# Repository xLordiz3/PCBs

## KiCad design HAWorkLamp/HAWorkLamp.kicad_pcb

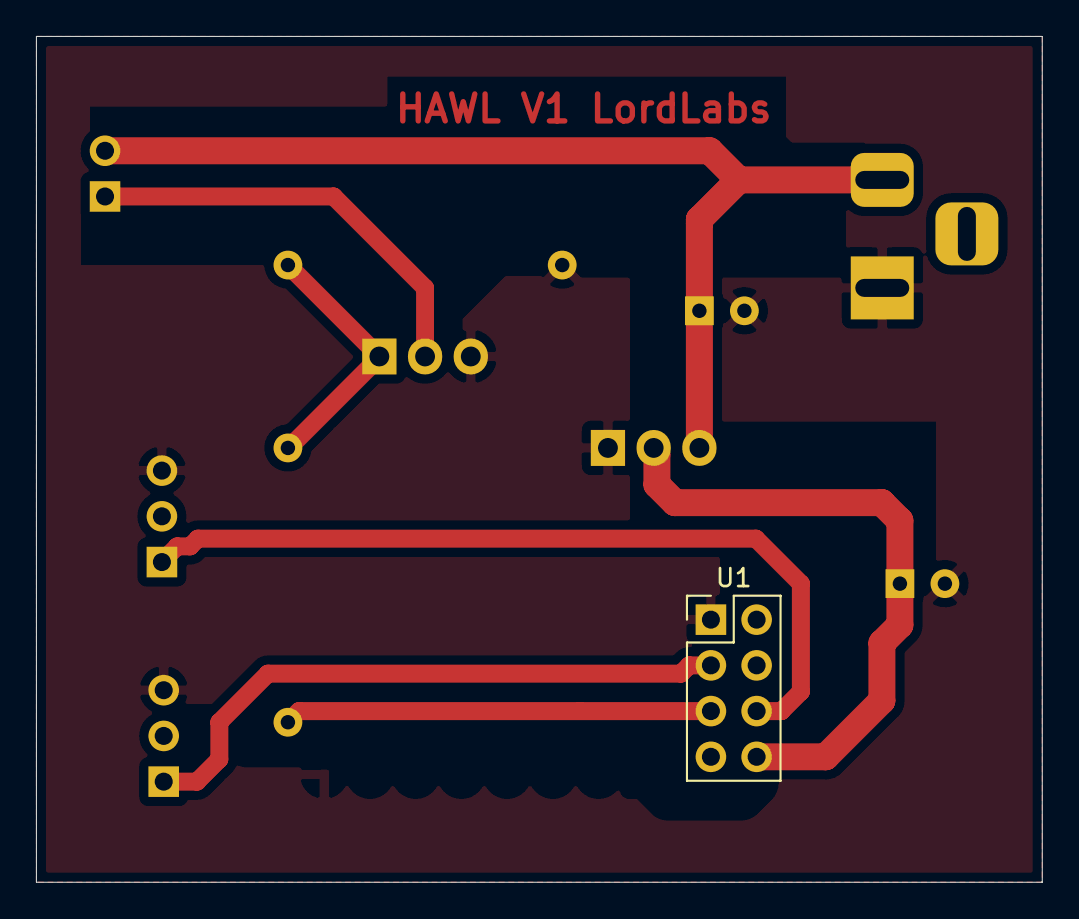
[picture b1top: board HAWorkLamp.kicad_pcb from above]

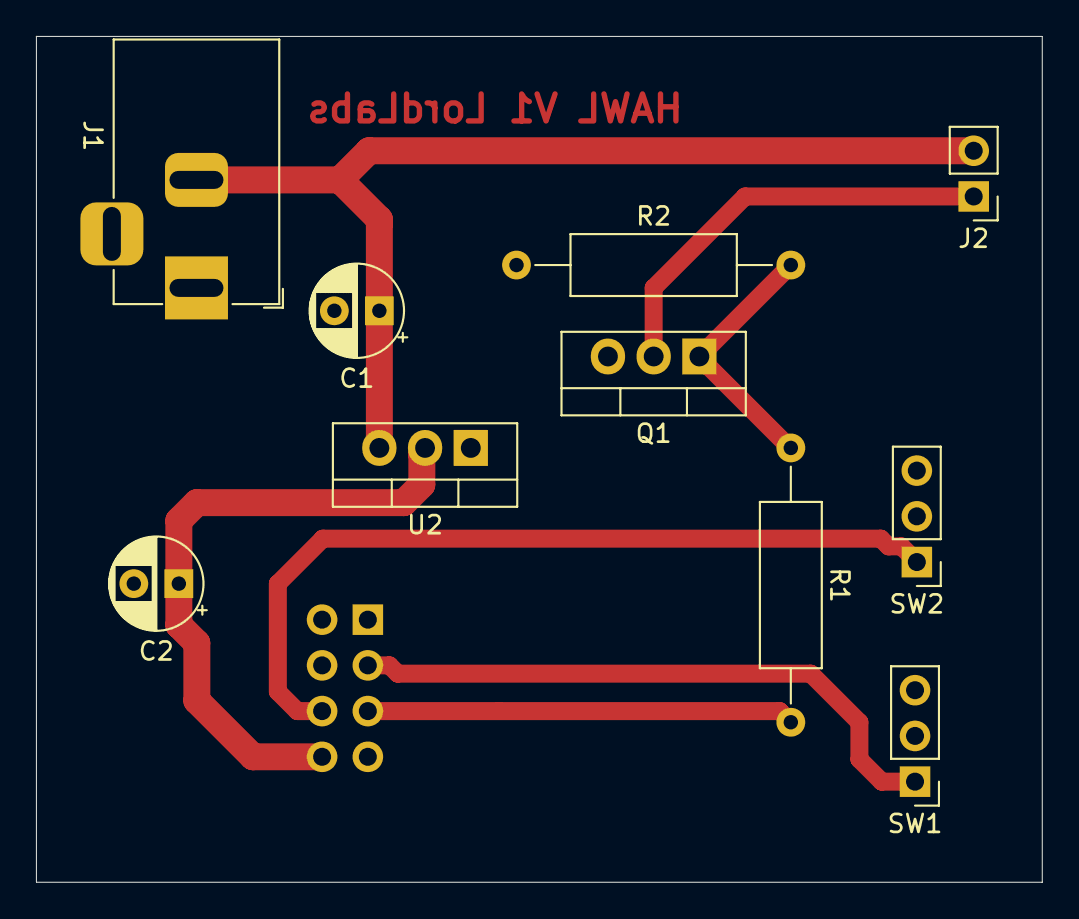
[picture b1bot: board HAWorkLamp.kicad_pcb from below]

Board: 2 copper layers, 55.9 x 47.0 mm, 11 parts (10 on the bottom side), 8 nets.

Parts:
C1, C2: CP; CP_Radial_D5.0mm_P2.50mm
J1: Jack-DC; BarrelJack_Horizontal
J2: LED Connection; PinHeader_1x02_P2.54mm_Vertical
Q1: FQP30N06L; TO-220-3_Vertical
R1: 220R; R_Axial_DIN0309_L9.0mm_D3.2mm_P15.24mm_Horizontal
R2: 100K; R_Axial_DIN0309_L9.0mm_D3.2mm_P15.24mm_Horizontal
SW1: Power switch; PinHeader_1x03_P2.54mm_Vertical
SW2: Reset Switch; PinHeader_1x03_P2.54mm_Vertical
U1: ESP8266; PinHeader_2x04_P2.54mm_Vertical
U2: LM1117-3.3; TO-220-3_Vertical

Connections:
+3V3: C2.1, U1.8, U2.2
+12V: C1.1, J1.2, J2.2, U2.3
/GPIO0: R1.2, U1.5
/GPIO2: SW1.1, U1.3
/RST: SW2.1, U1.6
GND: C1.2, C2.2, J1.1, Q1.3, R2.1, SW1.2, SW2.2, U1.1, U2.1
unnamed: J2.1, Q1.2
unnamed: Q1.1, R1.1, R2.2

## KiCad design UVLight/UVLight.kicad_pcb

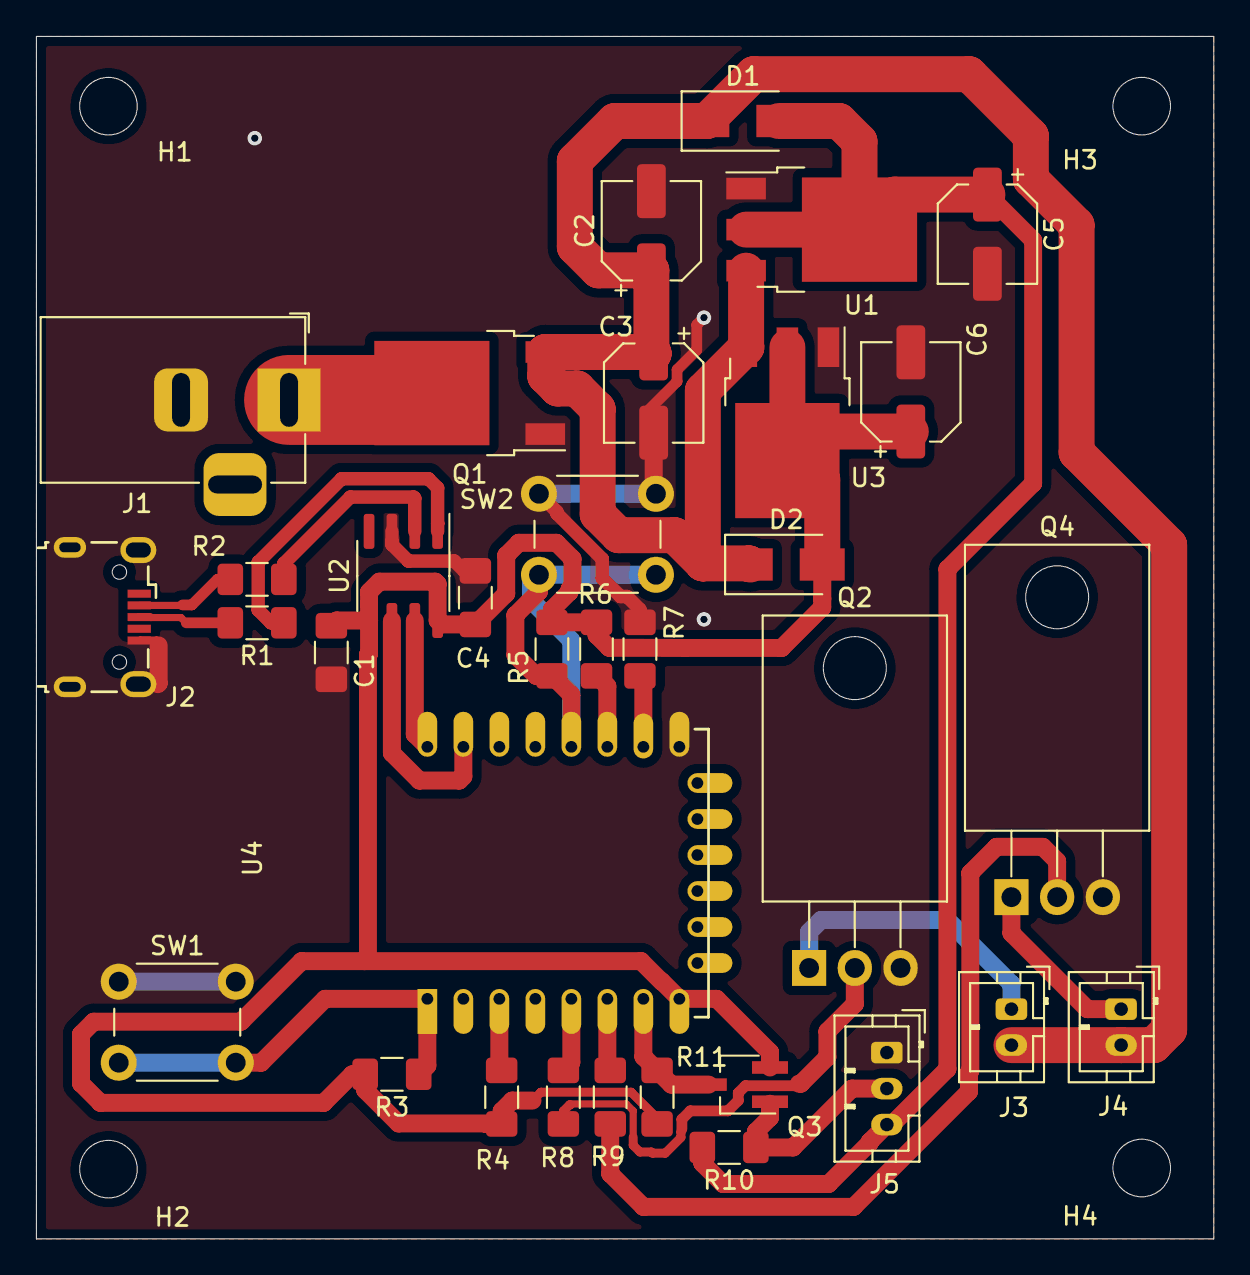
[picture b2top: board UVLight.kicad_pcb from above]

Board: 2 copper layers, 65.4 x 66.8 mm, 38 parts (0 on the bottom side), 24 nets.

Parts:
C1, C4: C 100nF; C_1206_3216Metric_Pad1.42x1.75mm_HandSolder
C2, C3, C5, C6: C 10uF; CP_Elec_5x5.4
D1, D2: 1N4002; D_SMA
H1, H2, H3, H4: MountingHole; MountingHole_3.2mm_M3
J1: Barrel_Jack_MountingPin; BarrelJack_Horizontal
J2: USB_B_Micro; USB_Micro-B_Wuerth_629105150521
J3, J4: Conn_01x02_Male; JST_PH_B2B-PH-K_1x02_P2.00mm_Vertical
J5: Conn_01x03_Male; JST_PH_B3B-PH-K_1x03_P2.00mm_Vertical
Q1: FQP47P06; TO-252-2
Q2, Q4: FQP30N06L; TO-220-3_Horizontal_TabDown
Q3: BS170; SOT-23W_Handsoldering
R1, R2: R 22; R_1206_3216Metric_Pad1.42x1.75mm_HandSolder
R3, R4, R5, R6, R7: R 10K; R_1206_3216Metric_Pad1.42x1.75mm_HandSolder
R8, R9: R; R_1206_3216Metric_Pad1.42x1.75mm_HandSolder
R10, R11: R 4.7K; R_1206_3216Metric_Pad1.42x1.75mm_HandSolder
SW1, SW2: SW_Push; SW_PUSH_6mm
U1: IFX27001TFV50ATMA1; TO-252-3_TabPin2
U2: CH330N; SOIC-8_3.9x4.9mm_P1.27mm
U3: IFX27001TFV33ATMA1; TO-252-3_TabPin2
U4: ESP-12E

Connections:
+3V3: C1.1, C4.1, C6.1, D2.2, Q3.2, R3.2, R4.2, R5.1, R6.1, R11.2, U2.5, U2.8, U3.2, U4.8
+5V: C5.1, D1.2, J5.3, R10.2, U1.2
+24V: C2.1, C3.1, D1.1, D2.1, J3.2, J4.2, Q1.3, U1.3, U3.3
/Fan: R8.2, U4.5
/RGB: Q3.3, R11.1, U4.7
/RX: U2.7, U4.16
/TX: U2.6, U4.15
/White: R9.2, U4.6
GND: C1.2, C2.2, C3.2, C4.2, C5.2, C6.2, J1.2, J2.5, J2.6, J5.1, Q1.1, Q2.3, Q4.3, R7.1, SW1.1, SW2.2, U1.1, U2.3, U3.1, U4.9
unnamed: J1.1, Q1.2
unnamed: J2.2, R2.2
unnamed: J2.3, R1.2
unnamed: J3.1, Q2.1
unnamed: J4.1, Q4.1
unnamed: J5.2, Q3.1, R10.1
unnamed: Q2.2, R8.1
unnamed: Q4.2, R9.1
unnamed: R1.1, U2.1
unnamed: R2.1, U2.2
unnamed: R3.1, SW1.2, U4.1
unnamed: R4.1, U4.3
unnamed: R5.2, SW2.1, U4.12
unnamed: R6.2, U4.11
unnamed: R7.2, U4.10

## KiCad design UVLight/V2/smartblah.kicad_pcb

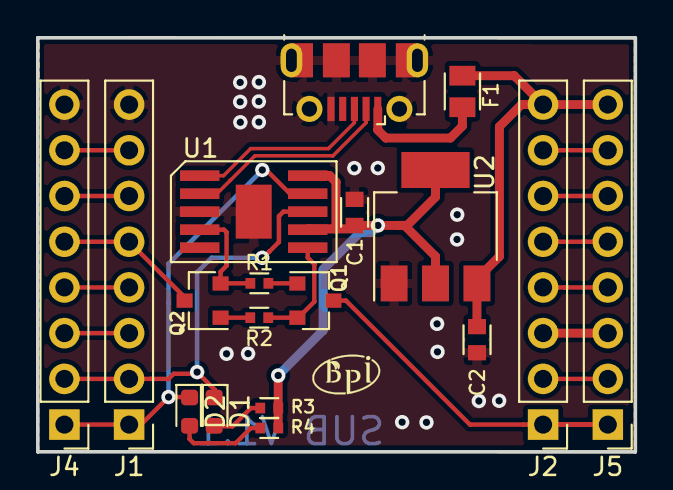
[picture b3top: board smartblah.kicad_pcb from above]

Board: 2 copper layers, 33.2 x 23.0 mm, 20 parts (1 on the bottom side), 26 nets.

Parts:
C1, C2: 10uF; C0603
D1, D2: LED-R; LED_0603_1608Metric
F1: Fuse 500mA; R0805
J1, J4: Smart-Pin-2; Pin_Header_Straight_1x08_Pitch2.54mm
J2, J5: Smart-Pin-1; Pin_Header_Straight_1x08_Pitch2.54mm
J3: USB_B_Micro; USB_Micro-B_Molex-105017-0001
O1: BPI-LOGO; bpi-logo
O2: Webduino-Logo; webduino-logo
Q1, Q2: MMBT3904; SOT-23
R1, R2, R3, R4: 1K; R0402
U1: CH340K; ESSOP-10
U2: AMS1117-3.3; SOT-223-3_TabPin2

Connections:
+3V3: C1.2, R3.1, R4.1, U1.7, U1.10, U2.2
/00: J1.5, J4.5, Q2.3
/02: J1.6, J4.6
/3V3: J2.3, J5.3
/04: J1.4, J4.4
/05: J1.3, J4.3
/12: J2.6, J5.6
/13: J2.7, J5.7
/14: J2.5, J5.5
/15: J1.7, J4.7
/16: J2.4, J5.4
/AD: J2.2, J5.2
/DTR: Q2.2, R1.1, U1.4
/RST: J2.1, J5.1, Q1.3
/RTS: Q1.2, R2.1, U1.6
/RX: D1.1, J1.2, J4.2, U1.8
/RXD: D2.1, J1.1, J4.1, U1.9
/UD+: J3.3, U1.1
/UD-: J3.2, U1.2
GND: C1.1, C2.1, J1.8, J3.5, J3.6, J4.8, U1.0, U1.3, U2.1
unnamed: D1.2, R3.2
unnamed: D2.2, R4.2
unnamed: F1.2, J3.1
unnamed: Q1.1, R1.2
unnamed: Q2.1, R2.2
VCC: C2.2, F1.1, J2.8, J5.8, U2.3

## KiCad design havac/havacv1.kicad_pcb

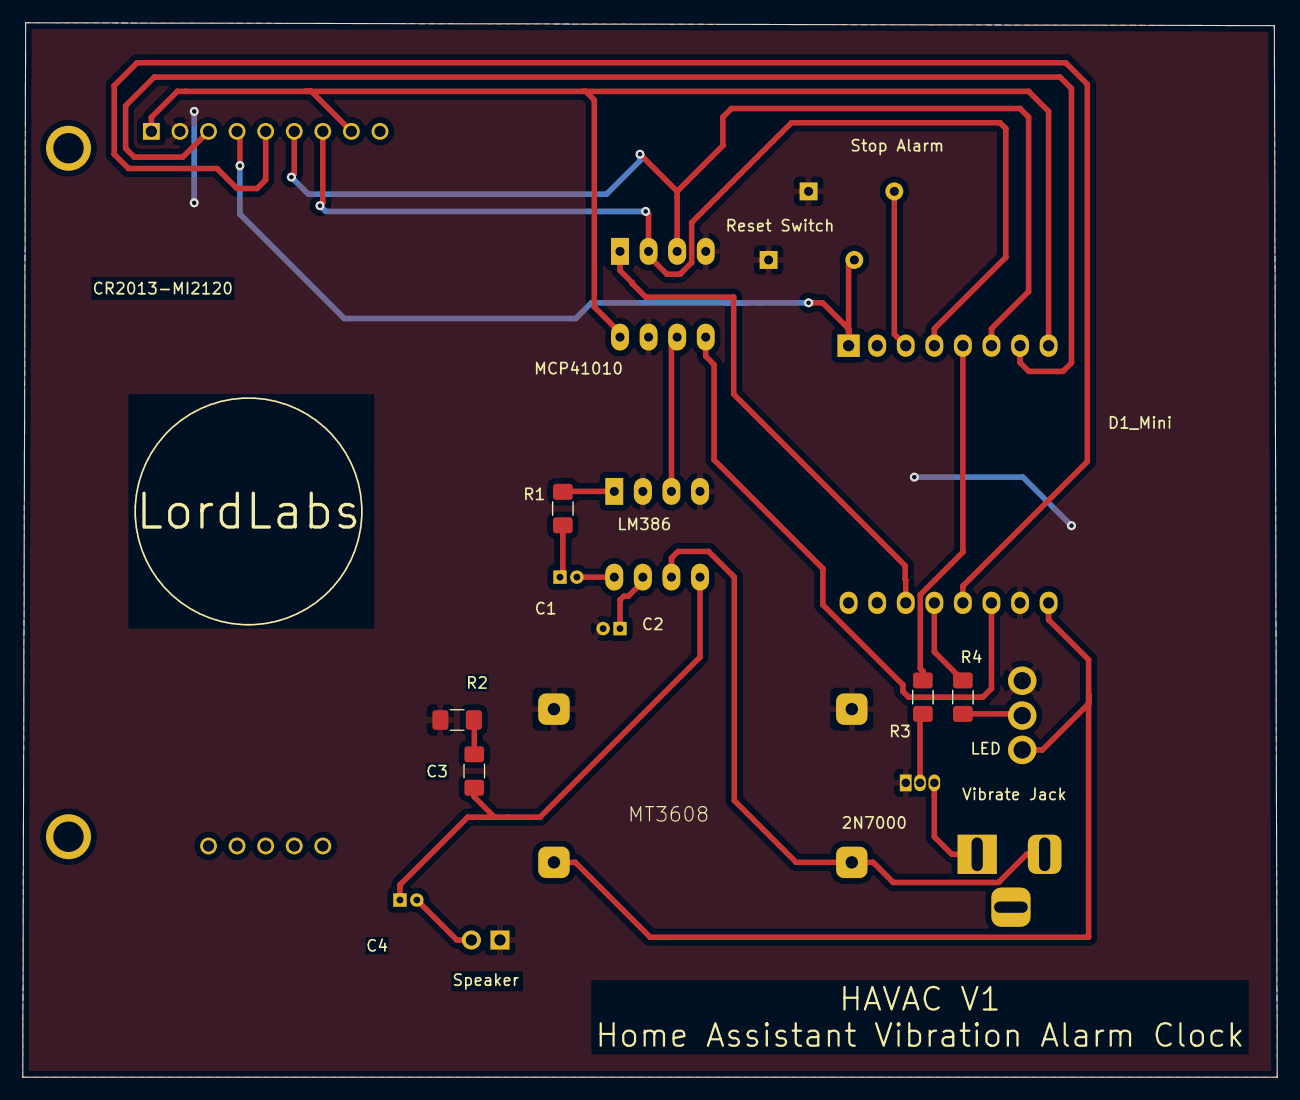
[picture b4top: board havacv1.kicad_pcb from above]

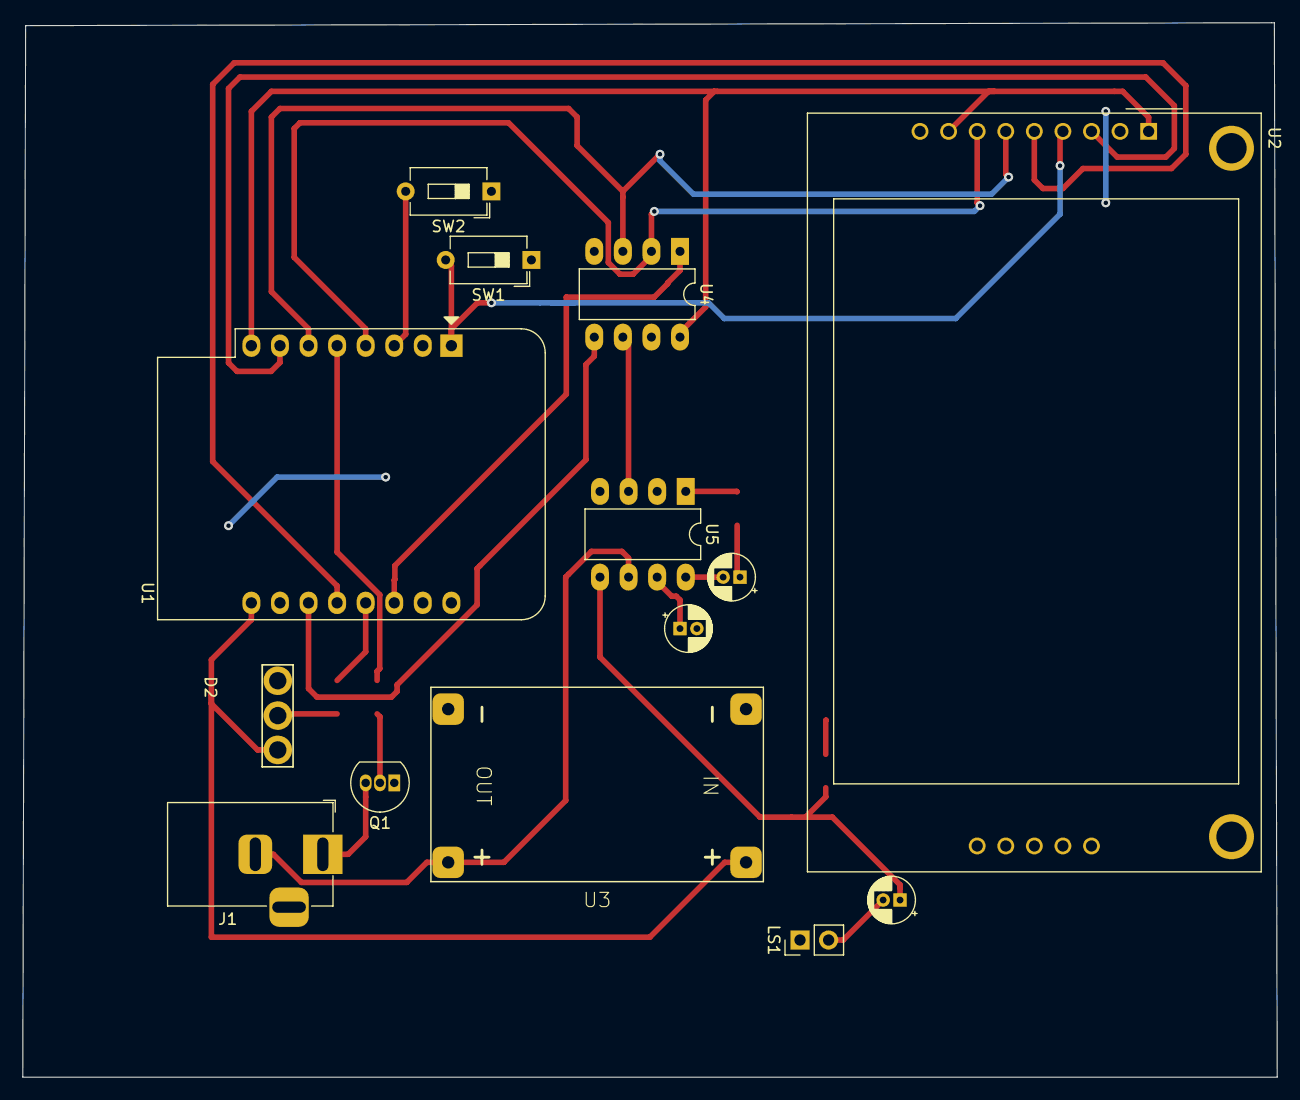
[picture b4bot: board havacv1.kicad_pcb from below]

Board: 2 copper layers, 111.5 x 93.7 mm, 19 parts (14 on the bottom side), 25 nets.

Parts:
C1: CP 10μF; CP_Radial_D4.0mm_P1.50mm
C2: CP 47μF; CP_Radial_D4.0mm_P1.50mm
C3: C 0.47μF; C_1206_3216Metric_Pad1.42x1.75mm_HandSolder
C4: CP 220μF; CP_Radial_D4.0mm_P1.50mm
D2: LED; 3pin-rgbled-connector
J1: Vibrate Jack; BarrelJack_Horizontal
LS1: Speaker; PinHeader_1x02_P2.54mm_Vertical
Q1: 2N7000; TO-92_Inline
R1: R 1.2KΩ; R_1206_3216Metric_Pad1.42x1.75mm_HandSolder
R2: R 10Ω; R_1206_3216Metric_Pad1.42x1.75mm_HandSolder
R3: R 270Ω; R_1206_3216Metric_Pad1.42x1.75mm_HandSolder
R4: R 470Ω; R_1206_3216Metric_Pad1.42x1.75mm_HandSolder
SW1: Reset Switch; SW_DIP_SPSTx01_Slide_6.7x4.1mm_W7.62mm_P2.54mm_LowProfile
SW2: Stop Alarm; SW_DIP_SPSTx01_Slide_6.7x4.1mm_W7.62mm_P2.54mm_LowProfile
U1: D1_Mini; WEMOS_D1_mini_light
U2: CR2013-MI2120
U3: MT3608; DC-DC-STEP-UP-MT3608
U4: MCP41010; DIP-8_W7.62mm_LongPads
U5: LM386; DIP-8_W7.62mm_LongPads

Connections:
+3V3: U1.8, U2.1, U2.8, U4.8
+5V: D2.3, U1.9, U3.IN+
+12V: J1.2, U3.OUT+, U5.6
/AW: U1.11, U4.5
/CSA: U1.14, U4.1
/CSD: U1.7, U2.3
/DC: U1.12, U2.5
/LED: R4.1, U1.13
/MOSI: U1.6, U2.6, U4.3
/PAAO: U4.6, U5.3
/RST: SW1.2, U1.1, U2.4
/SCK: U1.4, U2.7, U4.2
/STPA: SW2.2, U1.3
/VJ: R3.2, U1.5
GND: C2.2, D2.1, LS1.1, Q1.1, R2.1, SW1.1, SW2.1, U1.10, U2.2, U3.IN-, U3.OUT-, U4.4, U4.7, U5.2, U5.4
unnamed: C1.1, R1.2
unnamed: C1.2, U5.8
unnamed: C2.1, U5.7
unnamed: C3.1, C4.1, U5.5
unnamed: C3.2, R2.2
unnamed: C4.2, LS1.2
unnamed: D2.2, R4.2
unnamed: J1.1, Q1.3
unnamed: Q1.2, R3.1
unnamed: R1.1, U5.1
